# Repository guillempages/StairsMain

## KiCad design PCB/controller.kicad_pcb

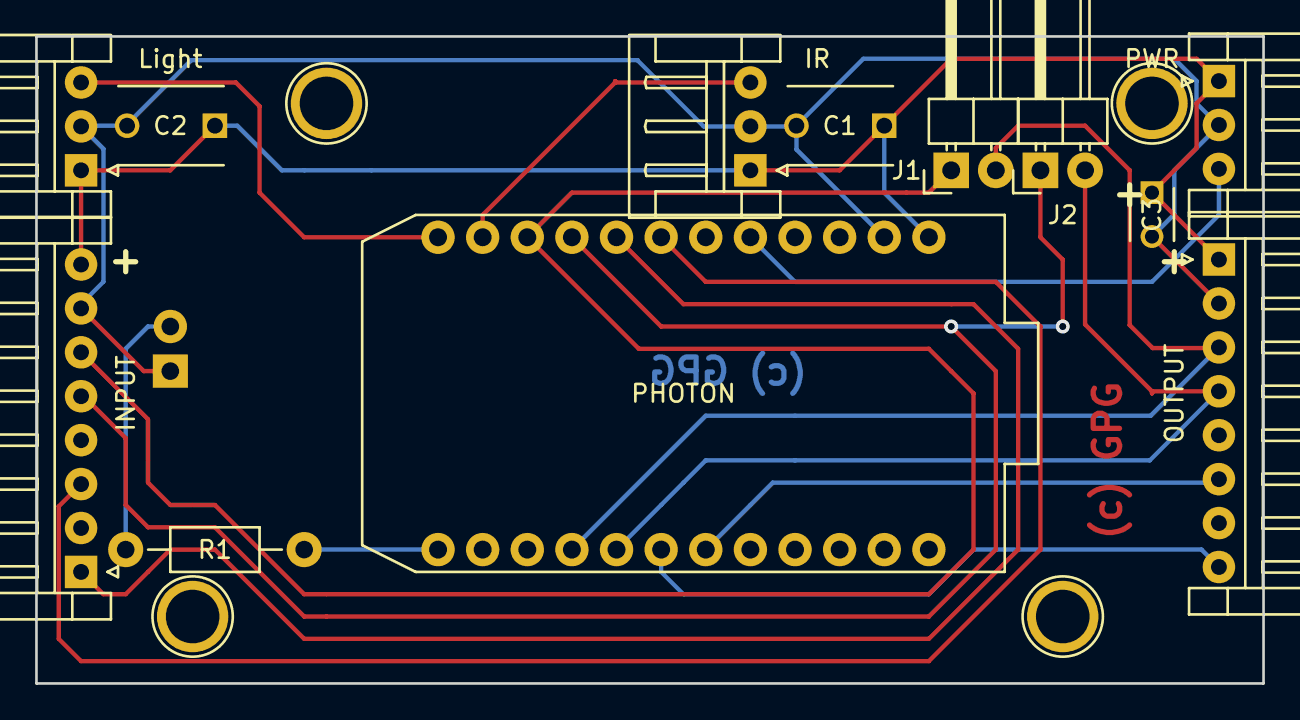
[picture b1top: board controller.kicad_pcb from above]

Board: 2 copper layers, 69.8 x 36.8 mm, 13 parts (1 on the bottom side), 15 nets.

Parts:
C1, C2: C; C_Disc_D6_P5
C3: CP1_Small; C_Disc_D3_P2.5
INPUT: CONN_01X08; JST_EH_S08B-EH_08x2.50mm_Angled
IR: CONN_01X03; JST_EH_S03B-EH_03x2.50mm_Angled
J1, J2: CONN_01X02; Pin_Header_Angled_1x02
LED: LED; LED-5MM
Light: CONN_01X03; JST_EH_S03B-EH_03x2.50mm_Angled
OUTPUT: CONN_01X08; JST_EH_S08B-EH_08x2.50mm_Angled
PHOTON: SPARK_CORE; photon
PWR: CONN_01X03; JST_EH_S03B-EH_03x2.50mm_Angled
R1: R; Resistor_Horizontal_RM10mm

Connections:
/CLK: J2.2, OUTPUT.4, PHOTON.17
/CLK1: INPUT.5, J2.1, PHOTON.9
/IR: IR.3, PHOTON.11
/LED: PHOTON.13, R1.2
/Light: Light.3, PHOTON.12
/MISO: OUTPUT.8, PHOTON.18
/MISO1: INPUT.1, PHOTON.8
/MOSI: OUTPUT.6, PHOTON.19
/MOSI1: INPUT.3, PHOTON.7
/PWR: PHOTON.5, PWR.3
/SS: J1.2, OUTPUT.3, PHOTON.16
/SS1: INPUT.6, J1.1, PHOTON.10
GND: C1.2, C2.2, C3.2, INPUT.7, IR.2, LED.1, Light.2, OUTPUT.2, PHOTON.2, PWR.2
unnamed: LED.2, R1.1
VCC: C1.1, C2.1, C3.1, INPUT.8, IR.1, Light.1, OUTPUT.1, PHOTON.1, PWR.1

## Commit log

2015-12-09 Add particle.ignore file
    Add ignore file, so that particle.dev can build.
2015-12-09 Update variable class
    "Spark" has been renamed to "Particle"
2015-12-09 Remove static id in single steps
    Somehow, having the static field does not compile. Removed the
    static modifier.
2015-12-09 Implement X-Mas mode.
    Fade LEDs on and off alternating.
2015-12-09 Use RGB LED as well for X-Mas mode
2015-12-10 Reduce SPI delays
    Move the SPI delay constants to config.h and reduce the delays.
2015-12-10 Implement running LightThreshold
    Add the code to implement running lights
2015-12-12 Implement multiple mode support
    Implement the possibility of having different modes.
    TODO: The running light/hole modes do not work yet
    TODO: The Blink mode si not implemented at all
    TODO: Fix timing of blink_alt mode (too fast)
2015-12-13 Finish multi-mode implementation
    Fix runningLight/Hole modes.
    Fix blinking delays.
    Implement blink mode.
2016-01-07 Send current mode
    Send the current mode as well as the current step count
2016-01-09 Low level TCP should not light LED
    Let the state machine take care of the connection LED,
    instead of the low level ip code.
2016-01-09 Add setMode method
2016-01-09 Add cloud variable for reading mode
2016-01-09 Implement net mode change
    Implement changing the mode over the network.
    Add (and use) virtual method to get the current mode.
2016-04-30 Add cloud function to change mode
2016-04-30 Ignore mode change requests for invalid mode
2016-04-30 Add disconnect method to Tcp class
2016-04-30 Implement Disconnect command
2016-04-30 Use index when writing chars
    Use an index variable, instead of hard-coding
    the bytes in the tcp state machine code; to
    make reordering the fields easier.
2016-05-01 Reformat code for legibility
    Add braces to the for loop.
2016-08-29 Change SPI pins
    Use the Photon's internal SPI pins for SPI.
2016-08-30 Add KiCad Files
2016-08-30 Delete photon_firmware_1472476287588.bin
    Should never have been there in the first place
2016-08-30 Add .gitignore
